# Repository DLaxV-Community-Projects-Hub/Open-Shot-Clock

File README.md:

# Open Shot Clock

Open Shot Clock is an Open Source and DIY Project aiming to minimize the barriers of entry for shot-clock-aided sports like Boxlacrosse and Sixes and maximizing the pure sports experience to an affordable price.

## Details

- 10" super bright LED digits (in color of your choice)
- indoor and outdoor usage
    - impact and water resistant portable design
    - LED brightness adjustable to your needs
- wireless and cable connection
- 12V input supply (portable battery or mains operation by AC-DC power supply)
- handheld controller
- wifi connection to smartphone
    - control option
    - settings change
    - firmware updates
- external horn for each display
- tripod stands ~2 meter height
- tested under competition conditions

The price tag is around 1000€ for materials and accessories. Depending on which design and battery options you choose, it might cost more.

For more information have a look at our [wiki](https://github.com/DLaxV-Community-Projects-Hub/Open-Shot-Clock/wiki/Open-Shot-Clock-Wiki) or this [blog](https://devdrik.de/blog/) made by [@devdrik](https://github.com/devdrik).

## The Open Shot Clock in Action

To see the Open Shot Clock in action check out the following recordings of Lacrosse high lights in Germany:

- [Men´s European Box Lacrosse Championship 2022 - Final: England vs. Germany](https://sportdeutschland.tv/germanylacrosse/european-box-lacrosse-championship-final-england-vs-germany) (face off at 0:07:20)
- [Women´s German Indoor Championchip 2023 - Final: HLC Rot-Weiss München vs. HTHC Hamburg A](https://sportdeutschland.tv/germanylacrosse/deutsche-indoor-lacrosse-meisterschaft-2023-finale) (draw at 0:07:35)
- [Men´s German Box Lacrosse Championchip 2023- Final: SG Süd vs. SC Frankfurt 1880](https://sportdeutschland.tv/germanylacrosse/deutsche-box-lacrosse-meisterschaft-2023-finale) (face off at 0:10:15)
- [Women´s German Indoor Championchip 2022 - Final: HLC Rot-Weiss München vs. HTHC Hamburg A](https://sportdeutschland.tv/germanylacrosse/finale-lacrosse-damen-indoor-meisterschaft-2022) (draw at 0:09:20)
- [Men´s German Box Lacrosse Championchip 2022- Final: Spreewölfe Berlin vs. KKHT SW Köln](https://sportdeutschland.tv/germanylacrosse/deutsche-meisterschaften-box-lacrosse-2022-spreewoelfe-berlin-vs-kkht-sw-koeln) (starting at Part 2)

## What´s Included Here

- Design Documentation for Open Shot Clock Displays and Controller
    - CAD and PCB designs
    - 3d printing files
    - DIY Building Instructions Manual (german)
    - BOM for Displays, Controller and accessories (german)
    - User Manual (german)
    - Source Code to run Displays and Controller
- Project Wiki (work in progress)

## Usage

To build your own Open Shot Clock you can find all documents/information in the [documentation](documentation/) folder.

### Getting All the Parts Needed

Please go through the BOM to make sure you have all parts needed available. In the BOM we have included recommendation links, where we recently purchased the parts. Be aware that you can choose from different design features which you have to cover in your purchases. The developement is stil ongoing so some design features are not yet tested or even sufficiently developed.

In the design 3d printing is requried. Make sure you print the necessary parts before starting to build or let them print by a printing service. Make sure the parts are printed with a heat and impact resistant 3d printing material. You can find recommended materials in the BOM.

For the PCBs you can use the design files to order them at a PCB manufacturer like [PCBWay](https://www.pcbway.com/) or you can get in touch with us, there are still some prototyping PCBs left of the current version. In the near future the PCB design has to be adapted to the new Heltec Lora 32 version 3.0. For now the new version is supported through a workaround. For more information check this [blog artical](https://devdrik.de/open-shot-clock-hannover/) from [@devdrik](https://github.com/devdrik).

### List of Optional Design Features:

- Displays - 19 mm thick highly machined base plate or 8 mm thick easy to build base plate
  - 19 mm makes a more stable design and is tested well
  - 8 mm base plate is much easier to build with less special machinery, but it´s not tested yet (there might be clashes with electronic parts inside the case)

- Displays - Temperature Managment (up to now we don´t know if a temperature management is necessary, to find out we integrated a temp sensor socket on the display pcbs, tests are still in planning)

  - No Cooling
  - Fan grids on the back for passiv cooling (default)
  - Active Fan with fan grids on the back (fan can be installed behind one fan grid and operated by one mosfet output, this feature is not yet included in the sourc code)

- Displays - Batteries (you can find different battery options in the BOM from which you can choose)
- Accessories - you can find different accessory options in the BOM from which you can choose
- Displays - Type-Plate customization (for having your own type-plate text you can get in touch with us, we can change the text for you)
- to be continued

### Assembling

When you have all parts available please follow the DIY Building Instructions Manual for assembling your Open Shot Clocks. Some parts like the base-, front- and back-plates or the aliminium extursion profiles need to be modified before they can be assembled. You can do the needed modification by using the drawings of these parts or you can get in touch with us, there are still some back plates left in our stock. In this [youtube playlist](https://www.youtube.com/watch?v=pQqHoa6__Ms&list=PLql27Iz3RF6tFwROZiCufJEf_9jadfyL8) you can see videos of [@devdrik](https://github.com/devdrik) performing the assembing process of an Open Shot Clock. In the future the playlist will be extended to cover all parts of the assembling process.

#### Heltec WiFi LoRa V2/V3

The V2 module is hard to get at the moment, so we added support for the new V3 version of the module, that is easy to source. To use V3 with PCBs designed for V2, you need to rewire some connections. So make sure not to use a V3 on a V2 PCB without modification!

What to do to use a V3 on a Display PCB v0.2:
- Do not connect GPIO21 and GPIO48 of the V3 to the display PCB
- Connect GPIO38 to the display PCB where GPIO21 would be
- Connect GPIO39 to the display PCB where GPIO48 would be
- In [config.h](code/display/include/config.h) set ```DISPLAY_PCB_VERSION V0_2_HACK```

What to do to use a V3 on a PCB for V2 (controller):
- Button BUTTON_PIN_B can not be used anymore
- Add pull-ups to all buttons (to be tested)

##### 5V Hack

Some Mosfet modules do not work with 3.3V on gate. To fix this on a v0.2 shotclock display PCB, we can disconnect the 3V3 pins from the of the heltec module and connect the corresponding pins on the display PCB to 5V of the heltec module.
This will bring all 3V3 on the display PCB to 5V, so be careful if you use a temperature sensor!

### How to Set Up the Firmware

You can find the source code for the controller and the displays in the code folder. Please just copy this repo to your VS Code with Plaformio extension and open both as projects. Fill in your preferred wifi credentials for setting up local device wifi networks to change settings. It is recommended to use different credentials for the controller and the displays to make sure you access the right devices settings.
Make sure to select the environment that fits the board you are using.

- flash controller
  - SPIFFS
  - source code
- flash displays
  - source code

## What´s Left to Do

- Tackle issues
- Build up Wiki with design insights, project history and roadmap
- Source code refactoring
- Design and test mdf display case as cost reduction opportunity
- pcb design to be ported to another open source platform and integration of heltc lora 32 v3.0 support
- Support first builders and gather feedback
- Offer english version of documents (if sufficiently demanded)
- to be continued

## How to Contribute

Feel free to customize your Open Shot Clock to your needs. For this purpose you can find the design files in the cad and pcb folders and the source code in the code folder. If you have ideas how to improve the Open Shot Clock and you need support for the integration or you want to share the benefits with the community please get in touch with us.

## Acknowledgement

Many thanks to [Ulf](https://github.com/ulf) for some initial inspiration in the approach to develop a LED shot clock. If you are looking out for a minimal and cheap setup for small indoor fields without obstacles have a look to [Ulf´s basketball shot clock tutotial](http://shotclock.de/)! With minor changes to the app it is possible to start with 30 seconds on the clock for lacrosse instead of 24 as for basketball. 

## Authors

- [@ChangeD20](https://github.com/ChangeD20)
- [@devdrik](https://github.com/devdrik)

## Contact

github@dlaxv.de

## License

[CERN OHL v2 Permissive](https://choosealicense.com/licenses/cern-ohl-p-2.0/)

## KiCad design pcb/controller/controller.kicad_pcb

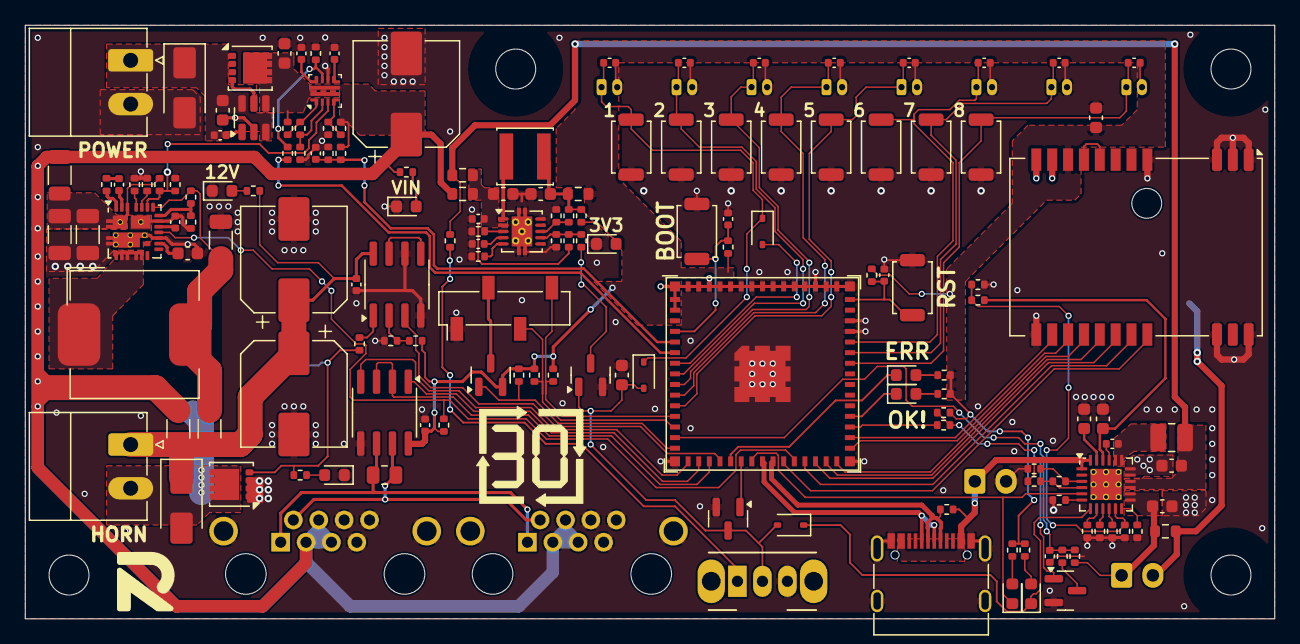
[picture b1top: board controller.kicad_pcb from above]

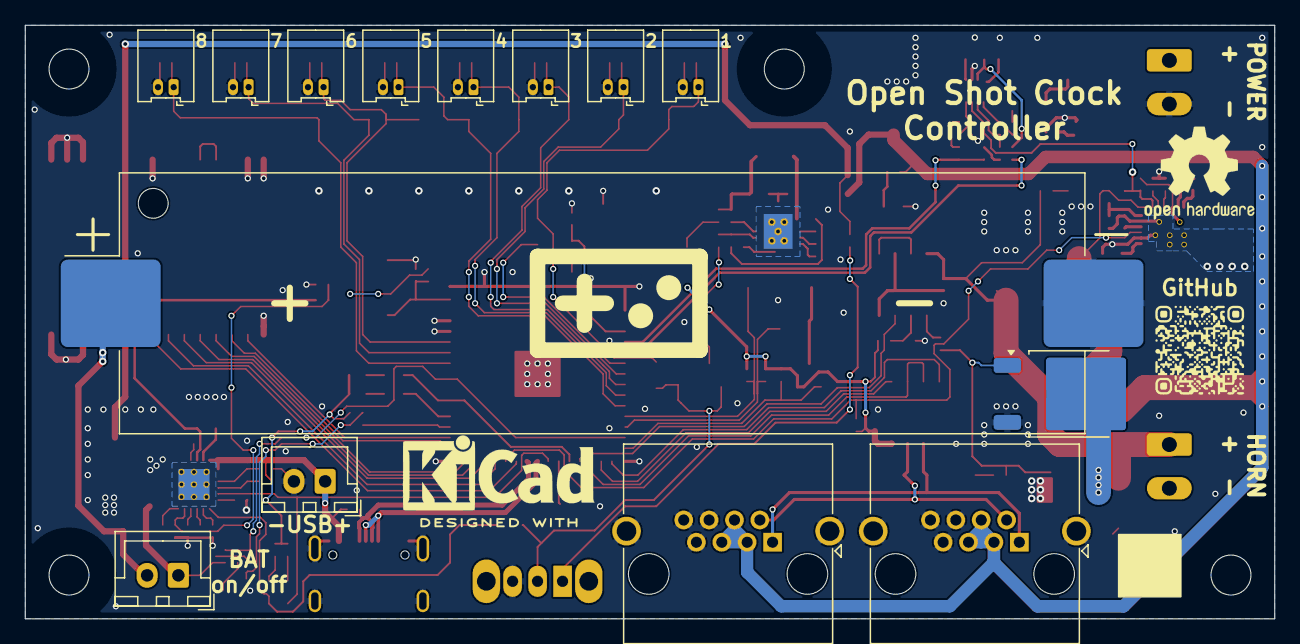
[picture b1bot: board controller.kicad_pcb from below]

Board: 2 copper layers, 100.0 x 47.5 mm, 168 parts (14 on the bottom side), 109 nets.

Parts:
BT401: 18650; BatteryHolder_SMD_1x18650
C101, C102, C201, C202, C203, C204, C205, C206, C207, C208, C209, C301, C401, C402, C408, C416, C417, C420, C426: 100n; C_0402_1005Metric
C302, C419, C421, C422, C423, C424, C425: 10u; C_0603_1608Metric
C403, C404, C418: 1u; C_0603_1608Metric
C405: 10n; C_0402_1005Metric
C406: 1n; C_0402_1005Metric
C407, C414, C415: 150u; CP_Elec_8x10
C409, C410, C413: 10u; C_1206_3216Metric
C411: 1u; C_0402_1005Metric
C412: 2u2; C_0603_1608Metric
D101, D102, D202, D402, D403, D406, D407, D408: LED; LED_0603_1608Metric
D201, D404, D405: 1N5819WS; D_SOD-323
D203: SS54; D_SMA
D401: SMAJ24CA; D_SMA
H101, H102, H103, H104: M3; MountingHole_3.2mm_M3
J101, J401: JST XH; JST_XH_B2B-XH-A_1x02_P2.50mm_Vertical
J102, J210: Term 3.5mm; PhoenixContact_MC_1,5_2-G-3.5_1x02_P3.50mm_Horizontal
J103, J104: RJ45; RJ45_Amphenol_RJHSE5380
J201: OLED 0.96" (I2C); PinSocket_1x04_P2.54mm_Vertical_SMD_Pin1Left
J202, J203, J204, J205, J206, J207, J208, J209: Picoblade; Molex_PicoBlade_53048-0210_1x02_P1.25mm_Horizontal
L401: 6.8uH; L_Bourns_SRP1050WA
L402: 100uH; L_Changjiang_FNR4030S
L403: 2.2uH; L_1008_2520Metric
P101: USB_C_Plug_USB2.0; USB_C_Receptacle_G-Switch_GT-USB-7010ASV
Q201: SI2301; SOT-23
Q202, Q401: DOZ35N06; VSON-8_3.3x3.3mm_P0.65mm_NexFET
Q203: Q_NMOS_GDS; TO-252-2
Q402, Q403, Q404: 2N7002; SOT-23
R101, R102, R103, R104, R107, R202, R410, R420, R421, R426, R429, R438, R439, R440, R446: 1k; R_0402_1005Metric
R105, R106, R416, R419, R448: 4k3; R_0402_1005Metric
R108, R436, R437, R443, R445, R447: 10k; R_0402_1005Metric
R201, R203, R205, R403, R404, R406, R407, R425, R444: 20k; R_0402_1005Metric
R204, R413, R441, R442: 560R; R_0402_1005Metric
R301: 120R; R_0805_2012Metric
R401, R402, R408: 0R; R_1206_3216Metric
R405: 2R2; R_0402_1005Metric
R409, R414, R415: 2k; R_0402_1005Metric
R411: 82k; R_0402_1005Metric
R412, R432, R449, R450: 0R; R_0402_1005Metric
R417, R418, R428, R430: 200k; R_0402_1005Metric
R422, R423, R424, R435: 0R; R_0603_1608Metric
R427, R431: 130k; R_0402_1005Metric
R433: 51k; R_0402_1005Metric
R434: 13k; R_0402_1005Metric
SW101, SW102, SW201, SW202, SW203, SW204, SW205, SW206, SW207, SW208: SW_4x3mm; SW_Push_4x3mm
SW401: SW_SPDT_312; SW_CuK_OS102011MA1QN1_SPDT_Angled
TH401: NTC; R_0402_1005Metric
U101: ESP32-S3-MINI-1; ESP32-S3-MINI-1U
U201: LM358; SOIC-8_3.9x4.9mm_P1.27mm
U301: SP3485EN-L/TR; SOIC-8_3.9x4.9mm_P1.27mm
U302: E220-400M22S
U401: SIC438BED-T1-GE3; Vishay_PowerPAK_MLP44-24L_ThermalVias
U402: TPS259474ARPW; RPW0010A_VQFN-HR-10
U403: LM74700; SOT-23-6
U404: LM5166DRCR; Texas_S-PVSON-N10_ThermalVias
U405: BQ25616; VQFN-24-1EP_4x4mm_P0.5mm_EP2.5x2.5mm_ThermalVias

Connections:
+3.3V: C301.1, C302.1, Q201.2 (S), R102.1, R103.1, R104.1, R105.1, R106.1, R107.1, R108.1, R201.1, R203.2, R420.1, R421.1, R424.2, R449.1, U101.3 (3V3), U301.8 (VCC), U302.9 (VCC)
+12V: C209.1, C414.1, C415.1, D203.1 (K), J210.1, R401.1, R408.2, R445.1, U201.8 (V+)
+BATT: C424.1, J401.1, R435.2, R448.2, U405.13 (BAT), U405.14 (BAT)
/12V_PG: R108.2, U101.26 (GPIO26), U401.14 (PGOOD)
/BOOT: C102.1, R107.2, SW102.1, U101.4 (GPIO0/BOOT)
/BTN_1: D201.2 (A), U101.7 (GPIO3/TOUCH3/ADC1_CH2)
/BTN_1_WKUP: C201.1, D201.1 (K), D405.1 (K), J202.1, SW201.1
/BTN_2: C202.1, J203.1, SW202.1, U101.8 (GPIO4/TOUCH4/ADC1_CH3)
/BTN_3: C205.1, J206.1, SW205.1, U101.9 (GPIO5/TOUCH5/ADC1_CH4)
/BTN_4: C206.1, J207.1, SW206.1, U101.10 (GPIO6/TOUCH6/ADC1_CH5)
/BTN_5: C207.1, J208.1, SW207.1, U101.11 (GPIO7/TOUCH7/ADC1_CH6)
/BTN_6: C208.1, J209.1, SW208.1, U101.41 (GPIO45)
/BTN_7: C204.1, J205.1, SW204.1, U101.40 (U0RXD/GPIO44/CLK_OUT2)
/BTN_8: C203.1, J204.1, SW203.1, U101.39 (U0TXD/GPIO43/CLK_OUT1)
/CHG_STAT: D403.1 (K), U101.22 (GPIO18/U1RXD/ADC2_CH7/CLK_OUT3), U405.5 (STAT)
/Communication/RS485.A: J103.1, J104.1, R301.2, U301.6 (A)
/Communication/RS485.B: J103.2, J104.2, R301.1, U301.7 (B)
/HORN: U101.19 (GPIO15/U0RTS/ADC2_CH4/XTAL_32K_P), U201.3 (+)
/I2C.SCL: J201.3, R106.2, U101.13 (GPIO9/TOUCH9/ADC1_CH8/FSPIHD/SUBSPIHD)
/I2C.SDA: J201.4, R105.2, U101.12 (GPIO8/TOUCH8/ADC1_CH7/SUBSPICS1)
/I_SENSE: R410.2, U101.6 (GPIO2/TOUCH2/ADC1_CH1)
/LED.ERR: D102.1 (K), U101.20 (GPIO16/U0CTS/ADC2_CH5/XTAL_32K_N)
/LED.OK: D101.1 (K), U101.34 (GPIO38/FSPIWP/SUBSPIWP)
/LORA.BUSY: U101.31 (SPIIO6/GPIO35/FSPID/SUBSPID), U302.14 (BUSY)
/LORA.IRQ: U101.32 (SPIIO7/GPIO36/FSPICLK/SUBSPICLK), U302.13 (DIO1)
/LORA.NSS: U101.25 (GPIO21), U302.19 (~NSS)
/LORA.RST: U101.30 (GPIO48/SPICLK_N/SUBSPICLK_N_DIFF), U302.15 (NRST)
/OLED_EN: Q201.1 (G), R201.2, U101.15 (GPIO11/TOUCH11/ADC2_CH0/FSPID/FSPIIO5/S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)
/PWR_SHDN: Q403.1 (G), U101.21 (GPIO17/U1TXD/ADC2_CH6)
/Power Supply/3V3_T: C421.1, L402.2, R424.1, R425.1, R446.1
/Power Supply/CHG_D+: R429.2, R438.1, U405.3 (D+)
/Power Supply/CHG_D-: R426.2, R429.1, U405.4 (D-)
/Power Supply/VUSB: J101.1, P101.A4 (VBUS), P101.A9 (VBUS), P101.B4 (VBUS), P101.B9 (VBUS), R101.1, R426.1, U405.1 (VAC), U405.24 (VBUS)
/Power Supply/~BQ_PG: D402.1 (K), D404.1 (K), U405.7 (~PG)
/SPI.CLK: U101.27 (GPIO47/SPICLK_P/SUBSPICLK_P_DIFF), U302.18 (SCK)
/SPI.MISO: U101.29 (SPIIO5/GPIO34/FSPICS0/SUBSPICS0), U302.16 (MISO)
/SPI.MOSI: U101.28 (SPIIO4/GPIO33/FSPIHD/SUBSPIHD), U302.17 (MOSI)
/UART.RX: U101.17 (GPIO13/TOUCH13/ADC2_CH2/FSPIQ/FSPIIO7/S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), U301.1 (RO)
/UART.TX: U101.16 (GPIO12/TOUCH12/ADC2_CH1/FSPICLK/FSPIIO6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), U301.4 (DI)
/UART.TXEN: U101.18 (GPIO14/TOUCH14/ADC2_CH3/FSPIWP/FSPIDQS/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), U301.2 (~RE), U301.3 (DE)
/USB.D+: P101.A6 (D+), P101.B6 (D+), R101.2, U101.24 (GPIO20/U1CTS/ADC2_CH9/CLK_OUT1/USB_D+)
/USB.D-: P101.A7 (D-), P101.B7 (D-), U101.23 (GPIO19/U1RTS/ADC2_CH8/CLK_OUT2/USB_D-)
/VBAT_SENSE: C426.2, R447.1, R448.1, U101.14 (GPIO10/TOUCH10/ADC1_CH9/FSPICS0/FSPIIO4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)
/VBAT_SENSE_EN: R450.1, U101.33 (SPIDQS/GPIO37/FSPIQ/SUBSPIQ)
/V_SENSE: C408.2, R407.2, R415.1, U101.5 (GPIO1/TOUCH1/ADC1_CH0)
GND: BT401.2 (-), C101.2, C102.2, C201.2, C202.2, C203.2, C204.2, C205.2, C206.2, C207.2, C208.2, C209.2, C301.2, C302.2, C403.2, C404.1, C405.1, C406.1, C407.2, C408.1, C409.2, C410.2, C411.2, C412.2, C413.2, C414.2, C415.2, C417.1, C418.2, C419.2, C420.1, C421.2, C422.2, C423.2, C424.2, C425.2, C426.1, D202.1 (K), D401.2 (A2), D406.1 (K), D407.1 (K), D408.1 (K), J101.2, J102.2, J103.6, J103.7, J103.8, J103.SH, J104.6, J104.7, J104.8, J104.SH, J201.1, J202.2, J203.2, J204.2, J205.2, J206.2, J207.2, J208.2, J209.2, P101.A1 (GND), P101.A12 (GND), P101.B1 (GND), P101.B12 (GND), P101.S1 (SHIELD), Q202.1 (S), Q202.2 (S), Q202.3 (S), Q203.3 (S), Q402.2 (S), Q403.2 (S), Q404.2 (S), R205.1, R412.2, R413.2, R414.2, R415.2, R416.1, R417.1, R418.1, R419.1, R431.2, R432.2, R433.2, R434.2, R437.2, R438.2, R439.2, R440.2, R441.2, R442.2, R443.2, SW101.2, SW102.2, SW201.2, SW202.2, SW203.2, SW204.2, SW205.2, SW206.2, SW207.2, SW208.2, SW401.3 (C), TH401.2, U101.1 (GND), U101.2 (GND), U101.42 (GND), U101.43 (GND), U101.46 (GND), U101.47 (GND), U101.48 (GND), U101.49 (GND), U101.50 (GND), U101.51 (GND), U101.52 (GND), U101.53 (GND), U101.54 (GND), U101.55 (GND), U101.56 (GND), U101.57 (GND), U101.58 (GND), U101.59 (GND), U101.60 (GND), U101.61 (GND), U101.62 (GND), U101.63 (GND), U101.64 (GND), U101.65 (GND), U201.4 (V-), U201.6 (-), U301.5 (GND), U302.1 (GND), U302.2 (GND), U302.3 (GND), U302.4 (GND), U302.10 (GND), U302.11 (GND), U302.12 (GND), U302.20 (GND), U302.22 (GND), U401.3 (PGND), U401.4 (PGND), U401.13 (PGND), U401.16 (AGND), U401.25 (AGND), U401.27 (PGND), U402.8 (GND), U403.2 (GND), U404.10 (GND), U404.11 (PAD), U405.17 (GND), U405.18 (GND), U405.25 (GND)
unnamed: BT401.1 (+), J401.2, R435.1
unnamed: C401.2, R405.1
unnamed: C416.1, L403.1, U405.19 (SW), U405.20 (SW)
unnamed: D101.2 (A), R102.2
unnamed: D102.2 (A), R103.2
unnamed: D202.2 (A), R202.2
unnamed: D203.2 (A), J210.2, Q202.5 (D), Q203.2 (D)
unnamed: D402.2 (A), R420.2
unnamed: D403.2 (A), R421.2
unnamed: C422.1, D404.2 (A), D405.2 (A), Q402.1 (G), Q403.3 (D), SW401.2 (B)
unnamed: D406.2 (A), R444.2
unnamed: D407.2 (A), R445.2
unnamed: D408.2 (A), R446.2
unnamed: J201.2, Q201.3 (D)
unnamed: Q202.4 (G), Q203.1 (G), R202.1, R204.2
unnamed: C404.2, Q401.5 (D), R404.1, U402.5 (IN), U403.4 (CATHODE)
unnamed: Q401.4 (G), U403.5 (GATE)
unnamed: Q402.3 (D), R430.2
unnamed: Q404.3 (D), R447.2
unnamed: Q404.1 (G), R449.2, R450.2
unnamed: R204.1, U201.1
unnamed: R427.1, SW401.1 (A)
unnamed: C101.1, R104.2, SW101.1, U101.45 (EN)
unnamed: R203.1, R205.2, U201.2 (-)
unnamed: U201.5 (+), U201.7
unnamed: U302.7 (TXEN), U302.8 (DIO2)
unnamed: C401.1, U401.23 (BOOT)
unnamed: R403.1, R416.2, U401.19 (EN), U402.3 (PG)
unnamed: R411.1, R419.2, U401.17 (FB)
unnamed: R418.2, U401.21 (MODE1)
unnamed: R417.2, U401.20 (MODE2)
unnamed: R405.2, U401.24 (PHASE)
unnamed: C411.1, U401.15 (VDD)
unnamed: C412.1, U401.12 (VDRV)
unnamed: C413.1, L401.2, R408.1, R411.2, U401.18 (VOUT)
unnamed: C406.2, U402.7 (DVDT)
unnamed: R404.2, R409.1, U402.1 (EN/UVLO)
unnamed: R410.1, R413.1, U402.9 (ILIM)
unnamed: C405.2, U402.10 (ITIMER)
unnamed: R409.2, R412.1, U402.2 (OVLO)
unnamed: R406.2, R414.1, U402.4 (PGTH)
unnamed: C402.2, U403.1 (VCAP)
unnamed: R428.2, R430.1, R431.1, U404.7 (EN)
unnamed: R425.2, R434.1, U404.8 (FB)
unnamed: R433.1, U404.3 (ILIM)
unnamed: R432.1, U404.5 (RT)
unnamed: C420.2, U404.4 (SS)
unnamed: L402.1, U404.1 (SW)
unnamed: C417.2, C418.1, R422.1, R423.1, R428.1, U404.2 (VIN)
unnamed: C416.2, U405.21 (BTST)
unnamed: R442.1, U405.10 (ICHG)
unnamed: R441.1, U405.8 (ILIM)
unnamed: R439.1, U405.6 (OTG)
unnamed: C425.1, U405.23 (PMID)
unnamed: C423.1, R436.1, U405.22 (REGN)
unnamed: R436.2, R437.1, TH401.1, U405.11 (TS)
unnamed: R443.1, U405.12 (VSET)
unnamed: R440.1, U405.9 (~CE)
SW: L401.1, U401.5 (SW), U401.6 (SW), U401.7 (SW), U401.8 (SW), U401.9 (SW)
VBUS: C407.1, J103.3, J103.4, J103.5, J104.3, J104.4, J104.5, R401.2, R402.1, R406.1, R407.1, R422.2, R444.1, U402.6 (OUT)
VEXT: C402.1, C403.1, D401.1 (A1), J102.1, Q401.1 (S), Q401.2 (S), Q401.3 (S), U403.3 (EN), U403.6 (ANODE)
VIN: C409.1, C410.1, R402.2, R403.2, U401.1 (VIN), U401.2 (VIN), U401.22 (VIN), U401.26 (VIN)
VSYS: C419.1, L403.2, R423.2, R427.2, U405.15 (SYS), U405.16 (SYS)

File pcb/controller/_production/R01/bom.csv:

Designator,Footprint,Quantity,Value,LCSC Part #
BT401,BatteryHolder_SMD_1x18650,1,18650, C2988620
"C101, C102, C201, C202, C203, C204, C205, C206, C207, C208, C209, C301, C401, C402, C408, C416, C417, C420, C426",0402,19,100n,C307331
"C302, C419, C421, C422, C423, C424, C425",0603,7,10u,C19702
"C403, C404, C418",0603,3,1u,C15849
C405,0402,1,10n,C15195
C406,0402,1,1n,C1523
"C407, C414, C415",CP_Elec_8x10,3,150u,C2898894
"C409, C410, C413",1206,3,10u,C13585
C411,0402,1,1u,C52923
C412,0603,1,2u2,C23630
"D101, D102, D202, D402, D403, D406, D407, D408",0603,8,LED,C2286
"D201, D404, D405",D_SOD-323,3,1N5819WS,C191023
D203,D_SMA,1,SS54,C22452
D401,D_SMA,1,SMAJ24CA,C20883150
"H101, H102, H103, H104",MountingHole_3.2mm_M3,4,M3,
"J102, J210","PhoenixContact_MC_1,5_2-G-3.5_1x02_P3.50mm_Horizontal",2,Term 3.5mm,C409115
"J103, J104",RJ45_Amphenol_RJHSE5380,2,RJ45,C19078599
J201,PinSocket_1x04_P2.54mm_Vertical_SMD_Pin1Left,1,"OLED 0.96"" (I2C)",C20071191
"J202, J203, J204, J205, J206, J207, J208, J209",Molex_PicoBlade_53048-0210_1x02_P1.25mm_Horizontal,8,Picoblade,C2845535
L401,L_Bourns_SRP1050WA,1,6.8uH,C32712978
L402,L_Changjiang_FNR4030S,1,100uH,C7588681
L403,1008,1,2.2uH,C964122
P101,USB_C_Receptacle_G-Switch_GT-USB-7010ASV,1,USB_C_Plug_USB2.0,C2927039
Q201,SOT-23,1,SI2301,C10487
"Q202, Q401",VSON-8_3.3x3.3mm_P0.65mm_NexFET,2,DOZ35N06,C36499167
"Q402, Q403, Q404",SOT-23,3,2N7002,C8545
"R102, R103, R104, R107, R202, R410, R420, R421, R429, R439, R440, R446",0402,12,1k,
"R105, R106, R416, R419, R448",0402,5,4k3,
"R108, R436, R437, R445, R447",0402,5,10k,
"R201, R203, R205, R403, R404, R406, R407, R425, R444",0402,9,20k,
"R204, R413, R441, R442",0402,4,560R,
R301,0805,1,120R,
"R402, R408",1206,2,0R,
R405,0402,1,2R2,
"R409, R414, R415",0402,3,2k,
R411,0402,1,82k,
"R412, R432, R449",0402,3,0R,
"R417, R418, R428, R430",0402,4,200k,
"R423, R424, R435",0603,3,0R,
"R427, R431",0402,2,130k,
R433,0402,1,51k,
R434,0402,1,13k,
"SW101, SW102, SW201, SW202, SW203, SW204, SW205, SW206, SW207, SW208",SW_Push_4x3mm,10,SW_4x3mm,C18078117
SW401,SW_CuK_OS102011MA1QN1_SPDT_Angled,1,SW_SPDT_312,C431548
U101,ESP32-S3-MINI-1U,1,ESP32-S3-MINI-1,C2980299
U201,SOIC-8_3.9x4.9mm_P1.27mm,1,LM358,C7950
U301,SOIC-8_3.9x4.9mm_P1.27mm,1,SP3485EN-L/TR,C8963
U302,E220-400M22S,1,E220-400M22S,C2971737
U401,Vishay_PowerPAK_MLP44-24L_ThermalVias,1,SIC438BED-T1-GE3,C511430
U402,RPW0010A_VQFN-HR-10,1,TPS259474ARPW,C3662807
U403,SOT-23-6,1,LM74700,C2941042
U404,Texas_S-PVSON-N10_ThermalVias,1,LM5166DRCR,C481392
U405,VQFN-24-1EP_4x4mm_P0.5mm_EP2.5x2.5mm_ThermalVias,1,BQ25616,C2866447

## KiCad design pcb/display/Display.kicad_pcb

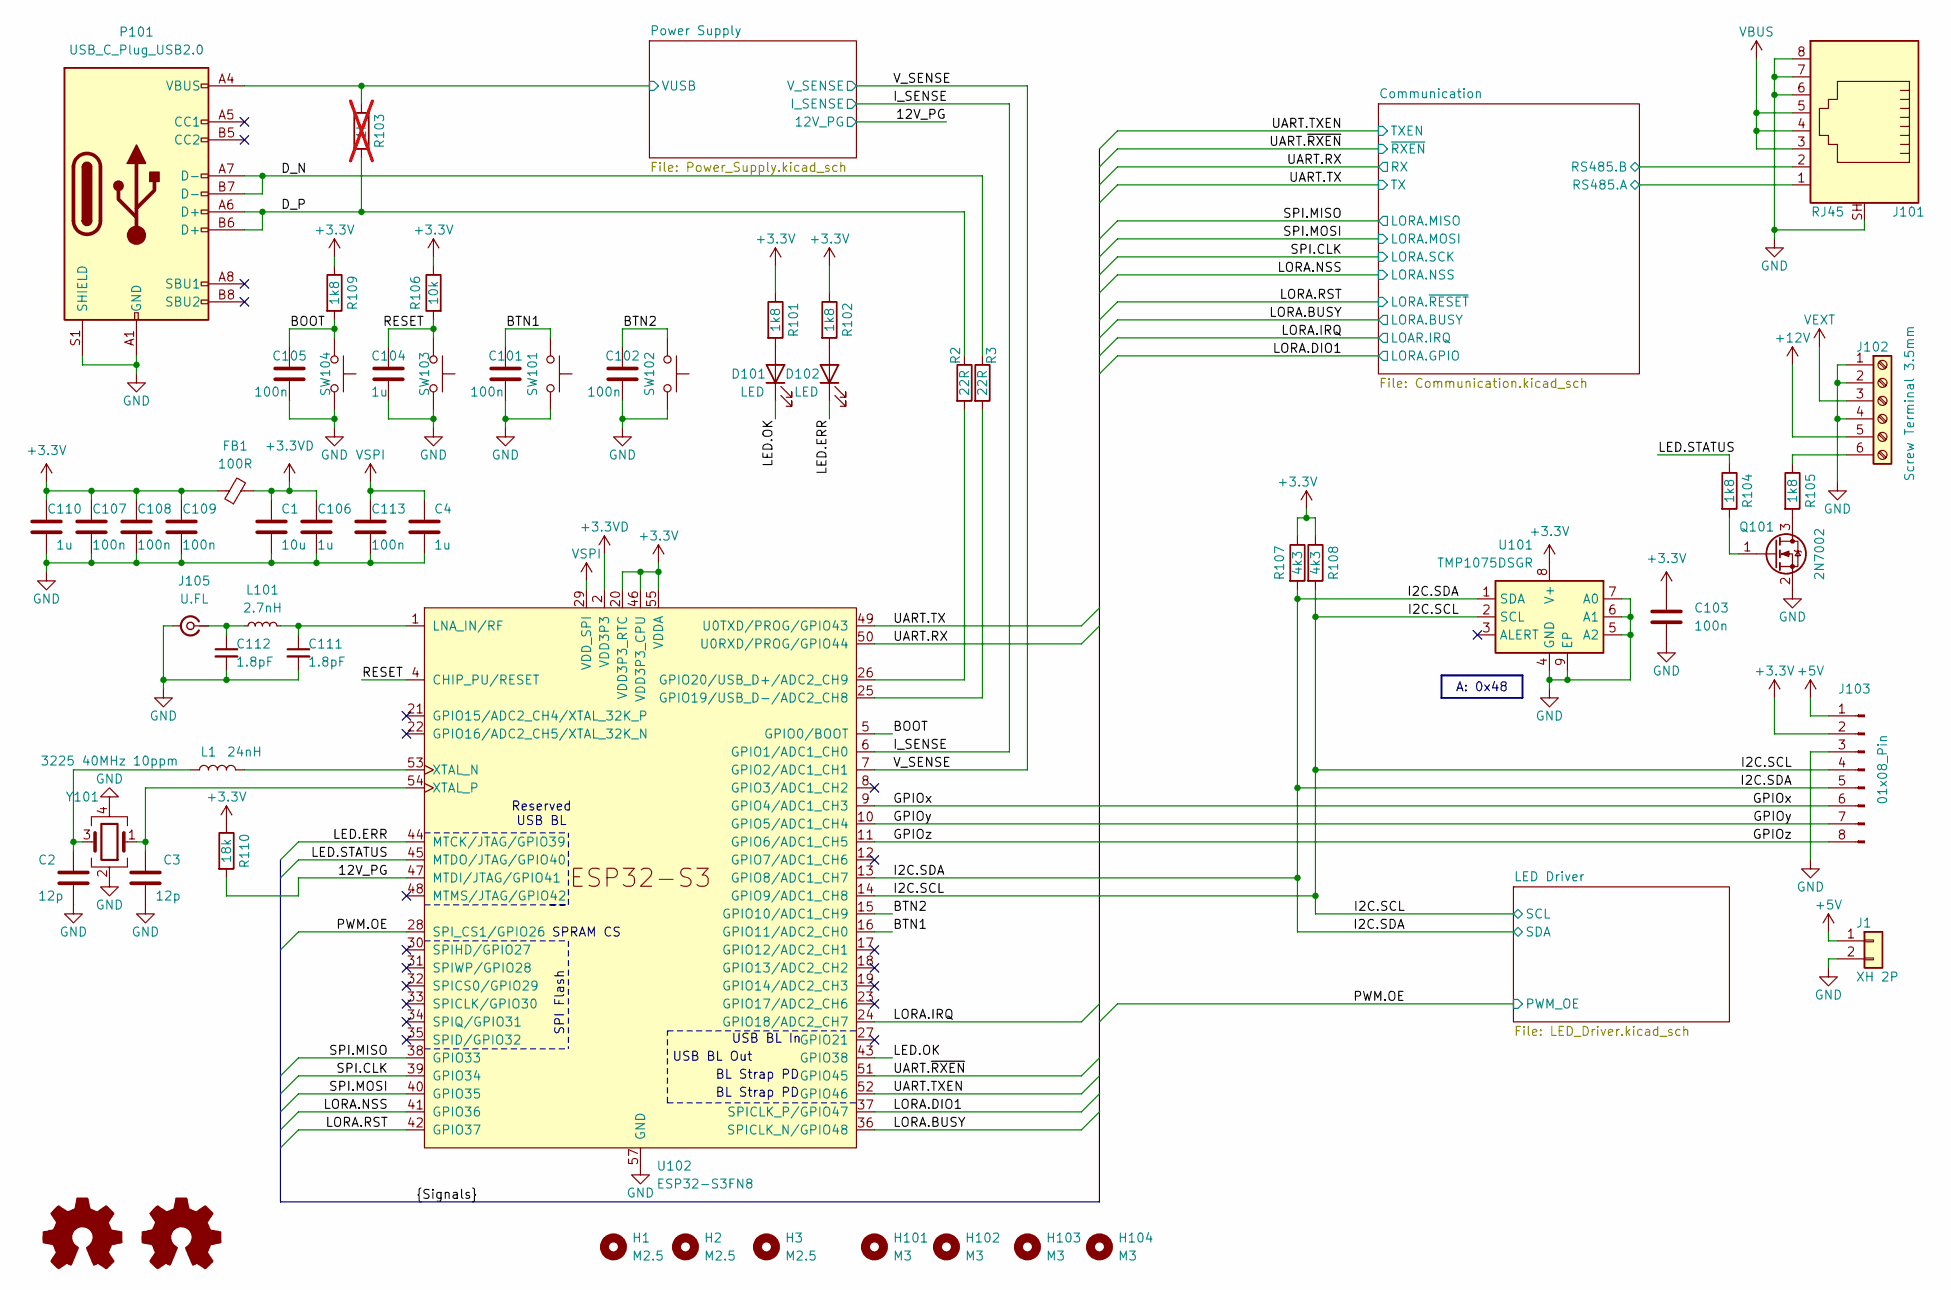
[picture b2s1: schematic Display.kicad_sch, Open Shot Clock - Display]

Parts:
C1: 10u; C_0603_1608Metric; LCSC Part # C19702
C2, C3: 12p; C_0402_1005Metric; LCSC Part # C76948
C4, C104, C106, C110: 1u; C_0402_1005Metric; LCSC Part # C52923
C101, C102, C103, C105, C107, C108, C109, C113: 100n; C_0402_1005Metric; LCSC Part # C307331
C111, C112: 1.8pF; C_0402_1005Metric; LCSC Part # C5186870
D101, D102: LED; LED_0603_1608Metric; LCSC Part # C2286
FB1: 100R; L_0603_1608Metric; LCSC Part # C14709
H1, H2, H3: M2.5; MountingHole_2.7mm_M2.5_DIN965
H101, H102, H103, H104: M3; MountingHole_3.2mm_M3
J1: XH 2P; JST_XH_B2B-XH-A_1x02_P2.50mm_Vertical; LCSC Part # C158012
J101: RJ45; RJ45_Amphenol_RJHSE5380; LCSC Part # C19078599
J102: Screw Terminal 3.5mm; PhoenixContact_MC_1,5_6-G-3.5_1x06_P3.50mm_Horizontal; LCSC Part # C409119
J103: 01x08_Pin; PinHeader_1x08_P2.54mm_Vertical; LCSC Part # C6332201
J105: U.FL; U.FL_Hirose_U.FL-R-SMT-1_Vertical; LCSC Part # C88374
L1: 24nH; L_0402_1005Metric; LCSC Part # C167472
L101: 2.7nH; L_0402_1005Metric; LCSC Part # C963981
P101: USB_C_Plug_USB2.0; USB_C_Receptacle_G-Switch_GT-USB-7010ASV; LCSC Part # C2927039
Q101: 2N7002; SOT-23; LCSC Part # C8545
R2, R3: 22R; R_0402_1005Metric
R101, R102, R104, R105, R109: 1k8; R_0402_1005Metric
R103: 1k; R_0402_1005Metric; not fitted
R106: 10k; R_0402_1005Metric
R107, R108: 4k3; R_0402_1005Metric
R110: 18k; R_0402_1005Metric
SW101, SW102, SW103, SW104: SW_4x3mm; SW_Push_4x3mm; LCSC Part # C18077679
SYM1: Logo_Open_Hardware_Small; OSHW-Logo2_7.3x6mm_SilkScreen
SYM2: Logo_Open_Hardware_Small; KiCad-Logo2_5mm_SilkScreen
U101: TMP1075DSGR; WSON-8-1EP_2x2mm_P0.5mm_EP0.9x1.6mm; LCSC Part # C2870250
U102: ESP32-S3FN8; QFN-56-1EP_7x7mm_P0.4mm_EP5.6x5.6mm; LCSC Part # C2913196
Y101: 3225 40MHz 10ppm; Crystal_SMD_3225-4Pin_3.2x2.5mm; LCSC Part # C37635388

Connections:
+3.3V: C103.1, C107.1, C108.1, C109.1, C110.1, FB1.1, J103.2, R101.1, R102.1, R106.1, R107.1, R108.1, R109.1, R110.1, U101.8 (V+), U102.20 (VDD3P3_RTC), U102.46 (VDD3P3_CPU), U102.55 (VDDA), U102.56 (VDDA); also elsewhere on the board
+3.3VD: C1.1, C106.1, FB1.2, U102.2 (VDD3P3), U102.3 (VDD3P3)
+5V: J1.1, J103.1; also elsewhere on the board
+12V: J102.5; also elsewhere on the board
/12V_PG: R110.2, U102.47 (MTDI/JTAG/GPIO41); also elsewhere on the board
/BOOT: C105.1, R109.2, SW104.1, U102.5 (GPIO0/BOOT)
/BTN1: C101.1, SW101.1, U102.16 (GPIO11/ADC2_CH0)
/BTN2: C102.1, SW102.1, U102.15 (GPIO10/ADC1_CH9)
/Communication/RS485.A: J101.1; also elsewhere on the board
/Communication/RS485.B: J101.2; also elsewhere on the board
/D_N: P101.A7 (D-), P101.B7 (D-), R3.1
/D_P: P101.A6 (D+), P101.B6 (D+), R2.1, R103.2
/GPIOx: J103.6, U102.9 (GPIO4/ADC1_CH3)
/GPIOy: J103.7, U102.10 (GPIO5/ADC1_CH4)
/GPIOz: J103.8, U102.11 (GPIO6/ADC1_CH5)
/I2C.SCL: J103.4, R108.2, U101.2 (SCL), U102.14 (GPIO9/ADC1_CH8); also elsewhere on the board
/I2C.SDA: J103.5, R107.2, U101.1 (SDA), U102.13 (GPIO8/ADC1_CH7); also elsewhere on the board
/I_SENSE: U102.6 (GPIO1/ADC1_CH0); also elsewhere on the board
/LED.ERR: D102.1 (K), U102.44 (MTCK/JTAG/GPIO39)
/LED.OK: D101.1 (K), U102.43 (GPIO38)
/LED.STATUS: R104.1, U102.45 (MTDO/JTAG/GPIO40)
/LORA.BUSY: U102.36 (SPICLK_N/GPIO48); also elsewhere on the board
/LORA.DIO1: U102.37 (SPICLK_P/GPIO47); also elsewhere on the board
/LORA.IRQ: U102.24 (GPIO18/ADC2_CH7); also elsewhere on the board
/LORA.NSS: U102.41 (GPIO36); also elsewhere on the board
/LORA.RST: U102.42 (GPIO37); also elsewhere on the board
/PWM.OE: U102.28 (SPI_CS1/GPIO26); also elsewhere on the board
/Power Supply/VUSB: P101.A4 (VBUS), P101.A9 (VBUS), P101.B4 (VBUS), P101.B9 (VBUS), R103.1; also elsewhere on the board
/RESET: C104.1, R106.2, SW103.1, U102.4 (CHIP_PU/RESET)
/SPI.CLK: U102.39 (GPIO34); also elsewhere on the board
/SPI.MISO: U102.38 (GPIO33); also elsewhere on the board
/SPI.MOSI: U102.40 (GPIO35); also elsewhere on the board
/UART.RX: U102.50 (U0RXD/PROG/GPIO44); also elsewhere on the board
/UART.TX: U102.49 (U0TXD/PROG/GPIO43); also elsewhere on the board
/UART.TXEN: U102.52 (GPIO46); also elsewhere on the board
/UART.~RXEN: U102.51 (GPIO45); also elsewhere on the board
/V_SENSE: U102.7 (GPIO2/ADC1_CH1); also elsewhere on the board
GND: C1.2, C2.2, C3.2, C4.2, C101.2, C102.2, C103.2, C104.2, C105.2, C106.2, C107.2, C108.2, C109.2, C110.2, C111.2, C112.2, C113.2, J1.2, J101.6, J101.7, J101.8, J101.SH, J102.1, J102.2, J102.4, J103.3, J105.2 (Ext), P101.A1 (GND), P101.A12 (GND), P101.B1 (GND), P101.B12 (GND), P101.S1 (SHIELD), Q101.2 (S), SW101.2, SW102.2, SW103.2, SW104.2, U101.4 (GND), U101.5 (A2), U101.6 (A1), U101.7 (A0), U101.9 (EP), U102.57 (GND), Y101.2, Y101.4; also elsewhere on the board
unnamed: C2.1, L1.1, Y101.3
unnamed: D101.2 (A), R101.2
unnamed: D102.2 (A), R102.2
unnamed: J102.6, R105.1
unnamed: C112.1, J105.1 (In), L101.1
unnamed: Q101.3 (D), R105.2
unnamed: Q101.1 (G), R104.2
unnamed: R3.2, U102.25 (GPIO19/USB_D-/ADC2_CH8)
unnamed: R2.2, U102.26 (GPIO20/USB_D+/ADC2_CH9)
unnamed: C111.1, L101.2, U102.1 (LNA_IN/RF)
unnamed: L1.2, U102.53 (XTAL_N)
unnamed: C3.1, U102.54 (XTAL_P), Y101.1
VBUS: J101.3, J101.4, J101.5; also elsewhere on the board
VEXT: J102.3; also elsewhere on the board
VSPI: C4.1, C113.1, U102.29 (VDD_SPI)

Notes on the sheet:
SPRAM CS
BL Strap PD
Reserved USB BL
USB BL In
SPI Flash
USB BL Out
A: 0x48

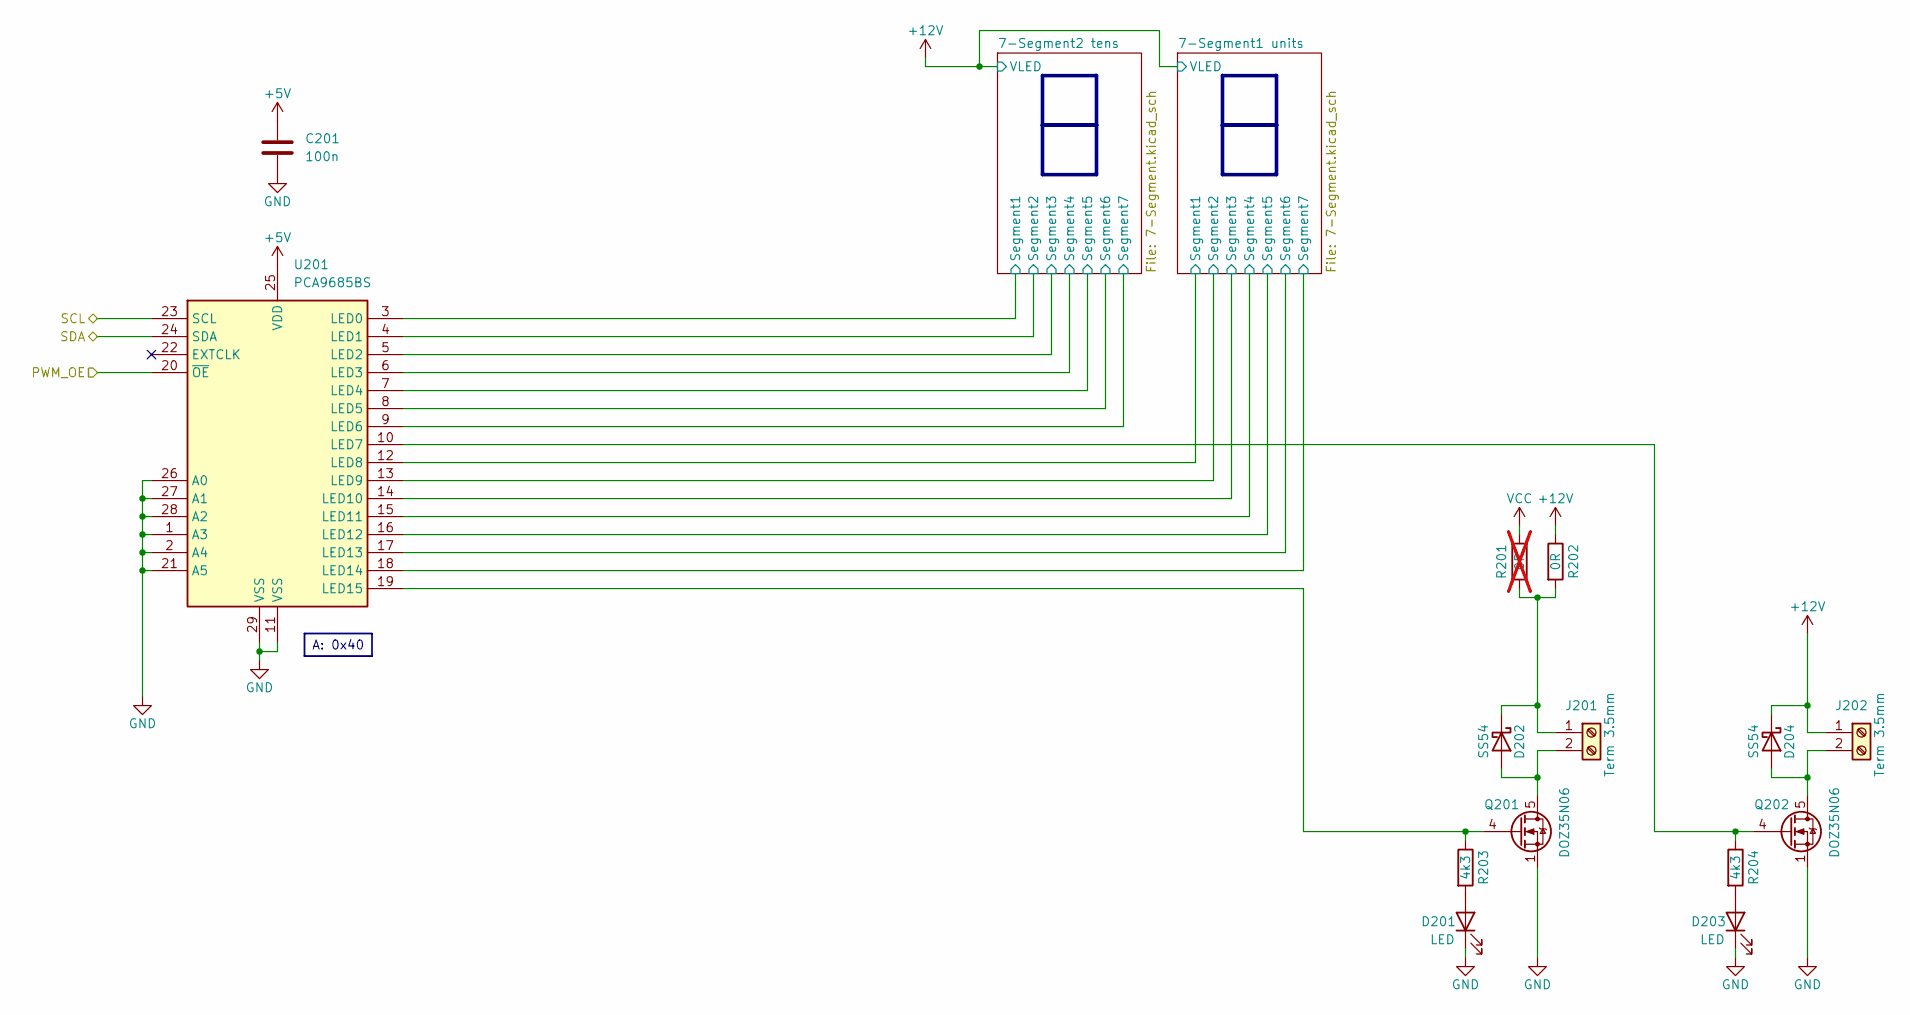
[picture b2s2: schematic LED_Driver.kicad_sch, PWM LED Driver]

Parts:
C201: 100n; C_0402_1005Metric; LCSC Part # C307331
D201, D203: LED; LED_0603_1608Metric; LCSC Part # C2286
D202, D204: SS54; D_SMA; LCSC Part # C22452
J201, J202: Term 3.5mm; PhoenixContact_MC_1,5_2-G-3.5_1x02_P3.50mm_Horizontal; LCSC Part # C409115
Q201, Q202: DOZ35N06; VSON-8_3.3x3.3mm_P0.65mm_Custom; LCSC Part # C36499167
R201: 0R; R_1206_3216Metric; not fitted
R202: 0R; R_1206_3216Metric
R203, R204: 4k3; R_0402_1005Metric
U201: PCA9685BS; QFN-28-1EP_6x6mm_P0.65mm_EP4.25x4.25mm; LCSC Part # C5191634

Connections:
+5V: C201.1, U201.25 (VDD); also elsewhere on the board
+12V: D204.1 (K), J202.1, R202.1; also elsewhere on the board
/I2C.SCL: U201.23 (SCL); also elsewhere on the board
/I2C.SDA: U201.24 (SDA); also elsewhere on the board
/LED Driver/7-Segment1 units/Segment1: U201.12 (LED8); also elsewhere on the board
/LED Driver/7-Segment1 units/Segment2: U201.13 (LED9); also elsewhere on the board
/LED Driver/7-Segment1 units/Segment3: U201.14 (LED10); also elsewhere on the board
/LED Driver/7-Segment1 units/Segment4: U201.15 (LED11); also elsewhere on the board
/LED Driver/7-Segment1 units/Segment5: U201.16 (LED12); also elsewhere on the board
/LED Driver/7-Segment1 units/Segment6: U201.17 (LED13); also elsewhere on the board
/LED Driver/7-Segment1 units/Segment7: U201.18 (LED14); also elsewhere on the board
/LED Driver/7-Segment2 tens/Segment1: U201.3 (LED0); also elsewhere on the board
/LED Driver/7-Segment2 tens/Segment2: U201.4 (LED1); also elsewhere on the board
/LED Driver/7-Segment2 tens/Segment3: U201.5 (LED2); also elsewhere on the board
/LED Driver/7-Segment2 tens/Segment4: U201.6 (LED3); also elsewhere on the board
/LED Driver/7-Segment2 tens/Segment5: U201.7 (LED4); also elsewhere on the board
/LED Driver/7-Segment2 tens/Segment6: U201.8 (LED5); also elsewhere on the board
/LED Driver/7-Segment2 tens/Segment7: U201.9 (LED6); also elsewhere on the board
/PWM.OE: U201.20 (~OE); also elsewhere on the board
GND: C201.2, D201.1 (K), D203.1 (K), Q201.1 (S), Q201.2 (S), Q201.3 (S), Q202.1 (S), Q202.2 (S), Q202.3 (S), U201.1 (A3), U201.2 (A4), U201.11 (VSS), U201.21 (A5), U201.26 (A0), U201.27 (A1), U201.28 (A2), U201.29 (VSS); also elsewhere on the board
unnamed: D201.2 (A), R203.2
unnamed: D202.2 (A), J201.2, Q201.5 (D)
unnamed: D202.1 (K), J201.1, R201.1, R202.2
unnamed: D203.2 (A), R204.2
unnamed: D204.2 (A), J202.2, Q202.5 (D)
unnamed: Q201.4 (G), R203.1, U201.19 (LED15)
unnamed: Q202.4 (G), R204.1, U201.10 (LED7)
VCC: R201.2; also elsewhere on the board

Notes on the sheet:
A: 0x40
